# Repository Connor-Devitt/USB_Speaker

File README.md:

# USB_Speaker
Electro-mechanical design for a  USB spaker

## Electrical Design
* Designed for single cable operation
* USB powered with on-board USB to audio DAC and stereo audio amplifier
* 2 18650 batteries for high power amplifier
* USB charges batteries when speaker is idle

### The Schematic (v0.1)

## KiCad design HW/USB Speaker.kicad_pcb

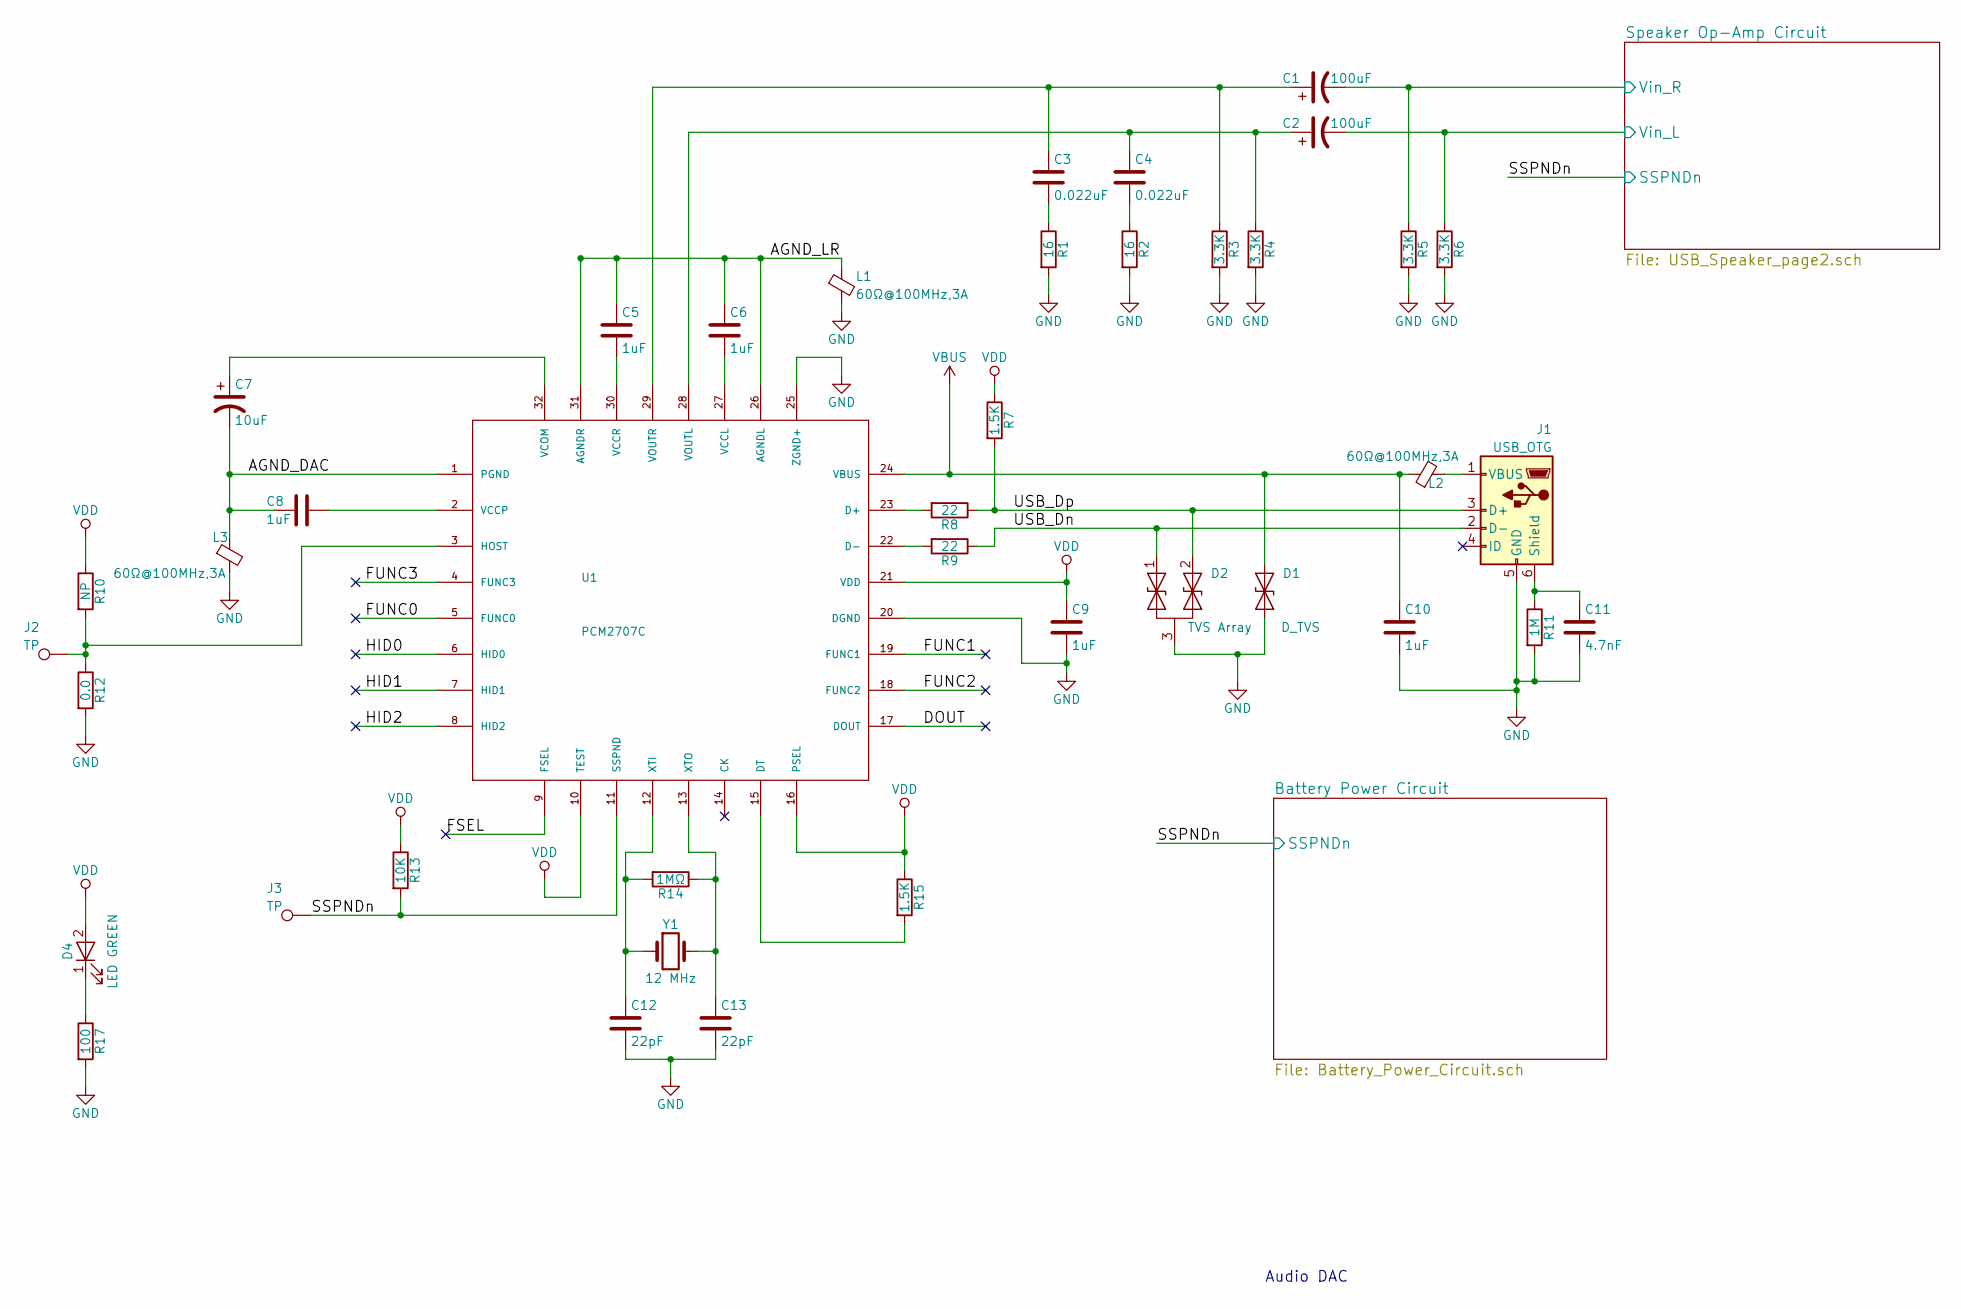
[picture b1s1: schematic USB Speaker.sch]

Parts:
C1, C2: 100uF; CP_Elec_6.3x5.7
C3, C4: 0.022uF; C_0805_HandSoldering
C5, C6, C8, C9, C10: 1uF; C_0805_HandSoldering
C7: 10uF; CP_Elec_6.3x5.7
C11: 4.7nF; C_0805_HandSoldering
C12, C13: 22pF; C_0805_HandSoldering
D1: D_TVS; D_SC79
D2: TVS Array; SOT-23
D4: LED GREEN; D_0805
J1: USB_OTG; USB_miniB_hirose_5S8
J2, J3: TP; Measurement_Point_Round-TH_Big
L1, L2, L3: 60Ω@100MHz,3A; L_0805_HandSoldering
R1, R2: 16; R_0805_HandSoldering
R3, R4, R5, R6: 3.3K; R_0805_HandSoldering
R7, R15: 1.5K; R_0805_HandSoldering
R8, R9: 22; R_0805_HandSoldering
R10: NP; R_0805_HandSoldering
R11: 1M; R_0805_HandSoldering
R12: 0.0; R_0805_HandSoldering
R13: 10K; R_0805_HandSoldering
R14: 1MΩ; R_0805_HandSoldering
R17: 100; R_0805_HandSoldering
U1: PCM2707C; TQFP-32_7x7mm_Pitch0.8mm
Y1: 12 MHz; Crystal_HC49-4H_Vertical

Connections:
/AGND_DAC: C7.2, C8.2, L3.1, U1.1 (PGND)
/AGND_LR: C5.1, C6.1, L1.1, U1.26 (AGNDL), U1.31 (AGNDR)
/DOUT: U1.17 (DOUT)
/FSEL: U1.9 (FSEL)
/FUNC0: U1.5 (FUNC0)
/FUNC1: U1.19 (FUNC1)
/FUNC2: U1.18 (FUNC2)
/FUNC3: U1.4 (FUNC3)
/HID0: U1.6 (HID0)
/HID1: U1.7 (HID1)
/HID2: U1.8 (HID2)
/SSPNDn: J3.1, R13.2, U1.11 (SSPND); also elsewhere on the board
/Speaker Op-Amp Circuit/Vin_L: C2.2, R6.1; also elsewhere on the board
/Speaker Op-Amp Circuit/Vin_R: C1.2, R5.1; also elsewhere on the board
/USB_Dn: D2.1 (A1), J1.2 (D-), R9.1
/USB_Dp: D2.2 (A2), J1.3 (D+), R7.2, R8.1
GND: C9.2, C10.2, C11.2, C12.2, C13.2, D1.1 (A1), D2.3 (common), J1.5 (GND), L1.2, L3.2, R1.2, R2.2, R3.2, R4.2, R5.2, R6.2, R11.2, R12.2, R17.2, U1.20 (DGND), U1.25 (ZGND+); also elsewhere on the board
unnamed: C1.1, C3.1, R3.1, U1.29 (VOUTR)
unnamed: C2.1, C4.1, R4.1, U1.28 (VOUTL)
unnamed: C3.2, R1.1
unnamed: C4.2, R2.1
unnamed: C5.2, U1.30 (VCCR)
unnamed: C6.2, U1.27 (VCCL)
unnamed: C7.1, U1.32 (VCOM)
unnamed: C8.1, U1.2 (VCCP)
unnamed: C11.1, J1.6 (Shield), R11.1
unnamed: C12.1, R14.2, U1.12 (XTI), Y1.1
unnamed: C13.1, R14.1, U1.13 (XTO), Y1.2
unnamed: D4.1 (K), R17.1
unnamed: J1.1 (VBUS), L2.2
unnamed: J2.1, R10.2, R12.1, U1.3 (HOST)
unnamed: R8.2, U1.23 (D+)
unnamed: R9.2, U1.22 (D-)
unnamed: R15.2, U1.15 (DT)
VBUS: C10.1, D1.2 (A2), L2.1, U1.24 (VBUS); also elsewhere on the board
VDD: C9.1, D4.2 (A), R7.1, R10.1, R13.1, R15.1, U1.10 (TEST), U1.16 (PSEL), U1.21 (VDD)

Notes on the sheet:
Audio DAC

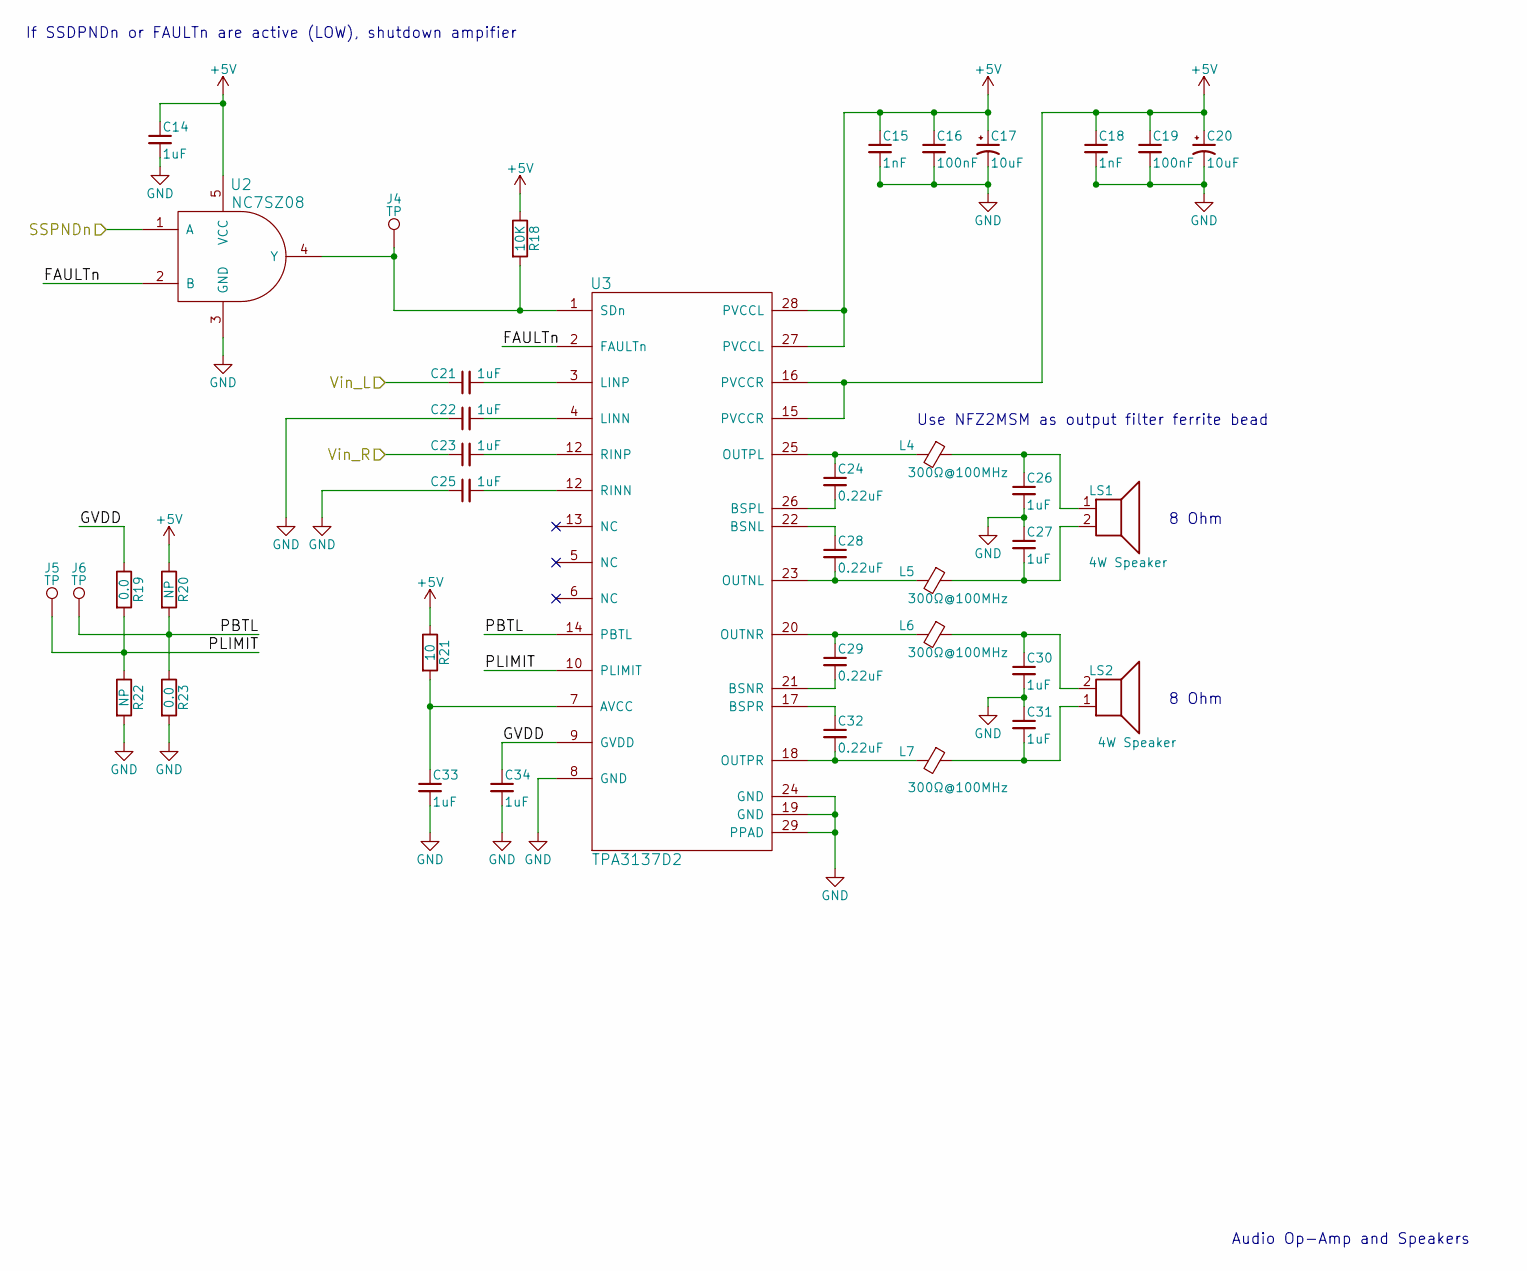
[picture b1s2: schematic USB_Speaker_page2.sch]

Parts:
C14, C21, C22, C23, C25, C26, C27, C30, C31, C33, C34: 1uF; C_0805_HandSoldering
C15, C18: 1nF; C_0805_HandSoldering
C16, C19: 100nF; C_0805_HandSoldering
C17, C20: 10uF; CP_Elec_6.3x5.7
C24, C28, C29, C32: 0.22uF; C_0805_HandSoldering
J4, J5, J6: TP; Measurement_Point_Round-TH_Big
L4, L5, L6, L7: 300Ω@100MHz; L_0805_HandSoldering
LS1, LS2: 4W Speaker; TerminalBlock_bornier-2_P5.08mm
R18: 10K; R_0805_HandSoldering
R19, R23: 0.0; R_0805_HandSoldering
R20, R22: NP; R_0805_HandSoldering
R21: 10; R_0805_HandSoldering
U2: NC7SZ08; SOT-23-5_HandSoldering
U3: TPA3137D2; TSSOP-28_4.4x9.7mm_Pitch0.65mm

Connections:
+5V: C14.1, C15.1, C16.1, C17.1, C18.1, C19.1, C20.1, R18.1, R20.1, R21.1, U2.5 (VCC), U3.15 (PVCCR), U3.16 (PVCCR), U3.27 (PVCCL), U3.28 (PVCCL); also elsewhere on the board
/SSPNDn: U2.1 (A); also elsewhere on the board
/Speaker Op-Amp Circuit/FAULTn: U2.2 (B), U3.2 (FAULTn)
/Speaker Op-Amp Circuit/GVDD: C34.1, R19.1, U3.9 (GVDD)
/Speaker Op-Amp Circuit/PBTL: J6.1, R20.2, R23.1, U3.14 (PBTL)
/Speaker Op-Amp Circuit/PLIMIT: J5.1, R19.2, R22.1, U3.10 (PLIMIT)
/Speaker Op-Amp Circuit/Vin_L: C21.1; also elsewhere on the board
/Speaker Op-Amp Circuit/Vin_R: C23.1; also elsewhere on the board
GND: C14.2, C15.2, C16.2, C17.2, C18.2, C19.2, C20.2, C22.1, C25.1, C26.2, C27.1, C30.2, C31.1, C33.2, C34.2, R22.2, R23.2, U2.3 (GND), U3.8 (GND), U3.19 (GND), U3.24 (GND), U3.29 (PPAD); also elsewhere on the board
unnamed: C21.2, U3.3 (LINP)
unnamed: C22.2, U3.4 (LINN)
unnamed: C24.1, L4.2, U3.25 (OUTPL)
unnamed: C24.2, U3.26 (BSPL)
unnamed: C26.1, L4.1, LS1.1
unnamed: C27.2, L5.1, LS1.2
unnamed: C28.1, U3.22 (BSNL)
unnamed: C28.2, L5.2, U3.23 (OUTNL)
unnamed: C29.1, L6.2, U3.20 (OUTNR)
unnamed: C29.2, U3.21 (BSNR)
unnamed: C30.1, L6.1, LS2.2
unnamed: C31.2, L7.1, LS2.1
unnamed: C32.1, U3.17 (BSPR)
unnamed: C32.2, L7.2, U3.18 (OUTPR)
unnamed: C33.1, R21.2, U3.7 (AVCC)
unnamed: J4.1, R18.2, U2.4 (Y), U3.1 (SDn)

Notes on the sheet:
Audio Op-Amp and Speakers
Use NFZ2MSM as output filter ferrite bead
If SSDPNDn or FAULTn are active (LOW), shutdown ampifier
8 Ohm

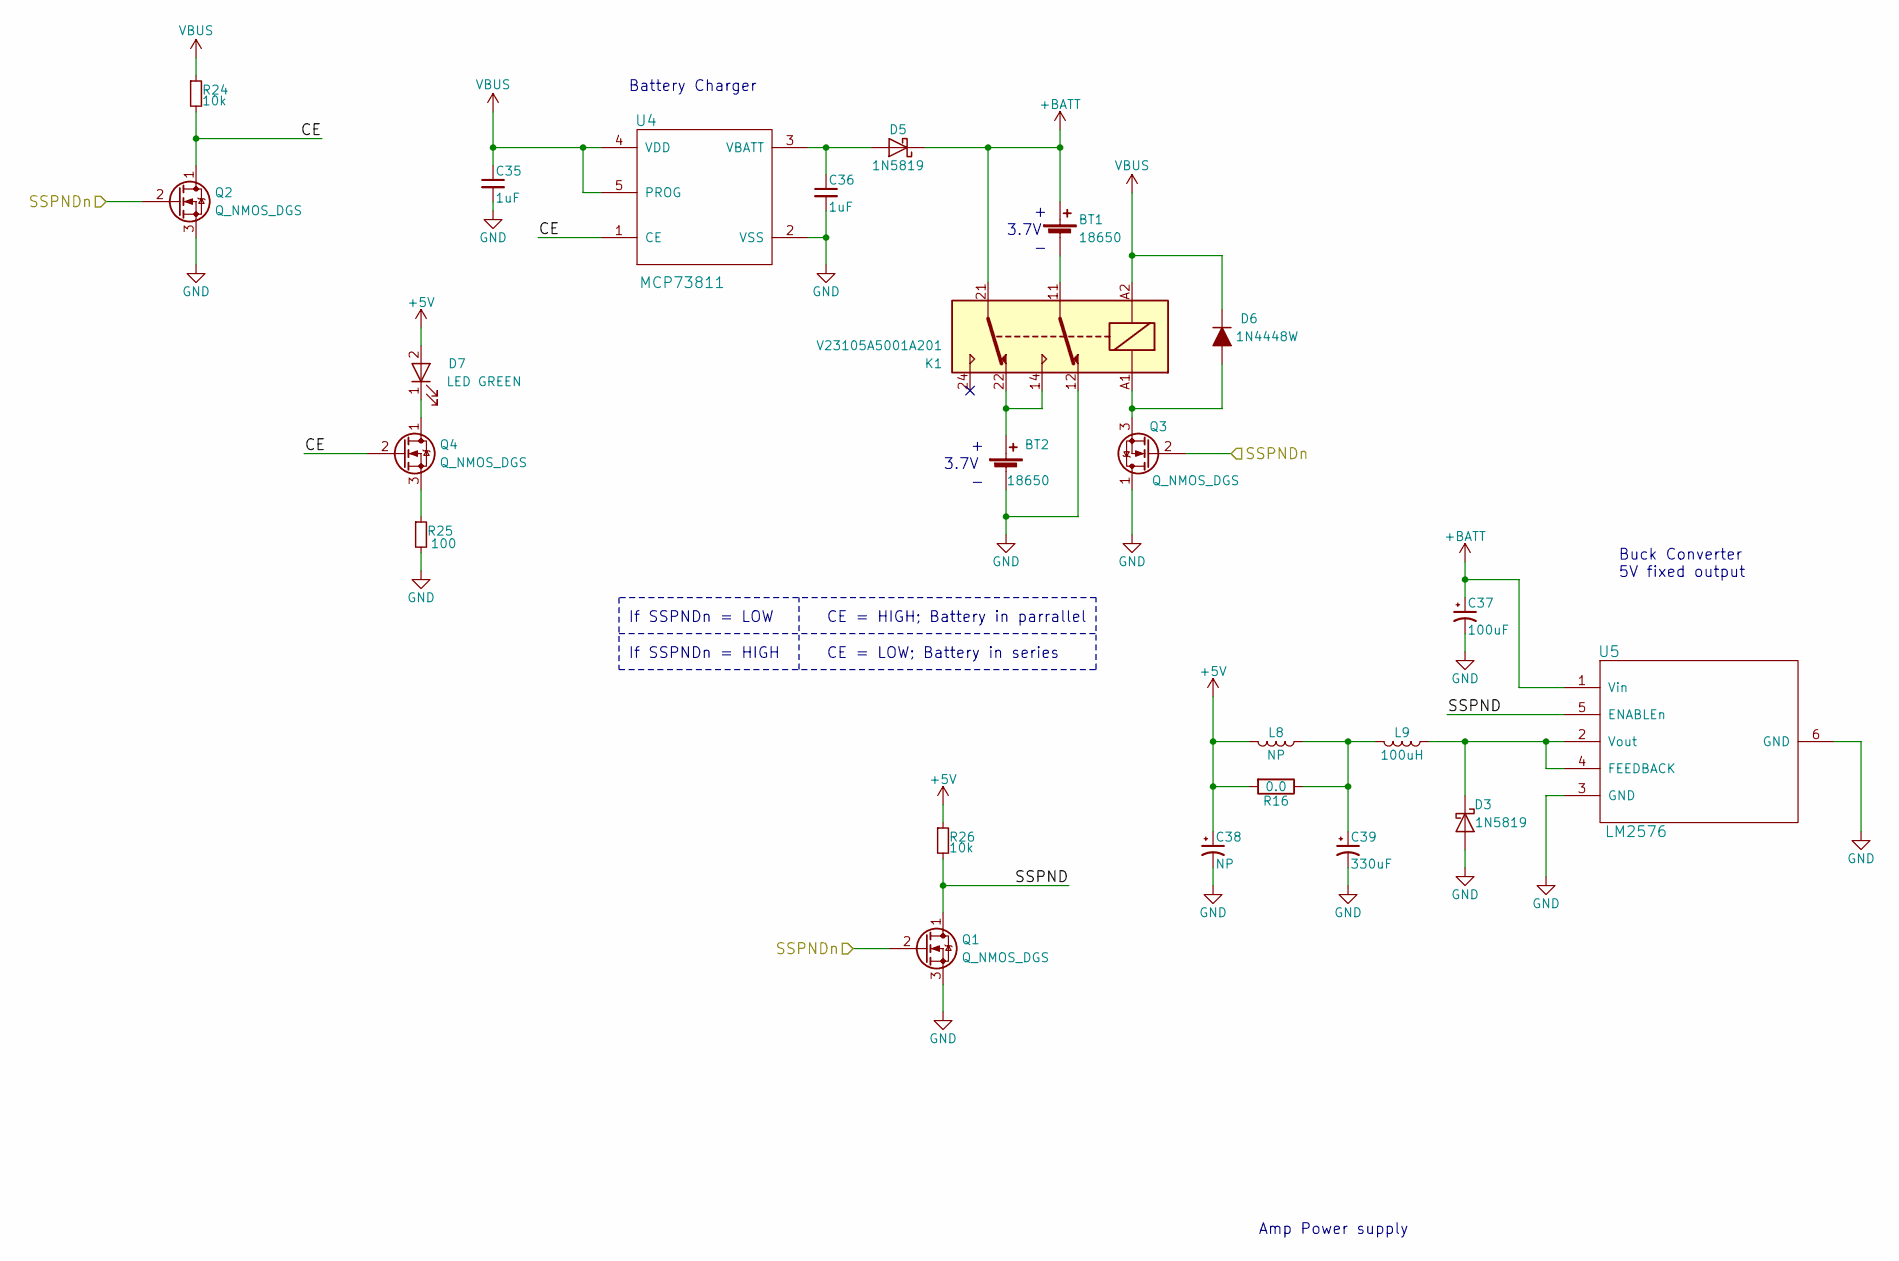
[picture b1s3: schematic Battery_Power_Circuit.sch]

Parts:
BT1, BT2: 18650; TerminalBlock_bornier-2_P5.08mm
C35, C36: 1uF; C_0805_HandSoldering
C37: 100uF; CP_Elec_6.3x5.7
C38: NP; CP_Elec_6.3x5.7
C39: 330uF; CP_Elec_6.3x7.7
D3, D5: 1N5819; D_SOD-123
D6: 1N4448W; D_SOD-123
D7: LED GREEN; D_0805
K1: V23105A5001A201; Relay_DPDT_Finder_40.52
L8: NP; L_12x12mm_h4.5mm
L9: 100uH; L_12x12mm_h8mm
Q1, Q2, Q3, Q4: Q_NMOS_DGS; SOT-23_Handsoldering
R16: 0.0; R_0805_HandSoldering
R24, R26: 10k; R_0805_HandSoldering
R25: 100; R_0805_HandSoldering
U4: MCP73811; SOT-23-5_HandSoldering
U5: LM2576; TO-263-5_TabPin6

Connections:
+5V: C38.1, D7.2 (A), L8.2, R16.2, R26.1; also elsewhere on the board
+BATT: BT1.1 (+), C37.1, D5.1 (K), K1.21, U5.1 (Vin)
/Battery Power Circuit/CE: Q2.1 (D), Q4.2 (G), R24.2, U4.1 (CE)
/Battery Power Circuit/SSPND: Q1.1 (D), R26.2, U5.5 (ENABLEn)
/SSPNDn: Q1.2 (G), Q2.2 (G), Q3.2 (G); also elsewhere on the board
GND: BT2.2 (-), C35.2, C36.2, C37.2, C38.2, C39.2, D3.2 (A), K1.12, Q1.3 (S), Q2.3 (S), Q3.1 (D), R25.2, U4.2 (VSS), U5.3 (GND), U5.6 (GND); also elsewhere on the board
unnamed: BT1.2 (-), K1.11
unnamed: BT2.1 (+), K1.14, K1.22
unnamed: C36.1, D5.2 (A), U4.3 (VBATT)
unnamed: C39.1, L8.1, L9.2, R16.1
unnamed: D3.1 (K), L9.1, U5.2 (Vout), U5.4 (FEEDBACK)
unnamed: D6.2 (A), K1.A1, Q3.3 (S)
unnamed: D7.1 (K), Q4.1 (D)
unnamed: Q4.3 (S), R25.1
VBUS: C35.1, D6.1 (K), K1.A2, R24.1, U4.4 (VDD), U4.5 (PROG); also elsewhere on the board

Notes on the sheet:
Amp Power supply
If SSPNDn = LOW
If SSPNDn = HIGH
CE = HIGH; Battery in parrallel
CE = LOW; Battery in series
3.7V
Battery Charger
Buck Converter 5V fixed output

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
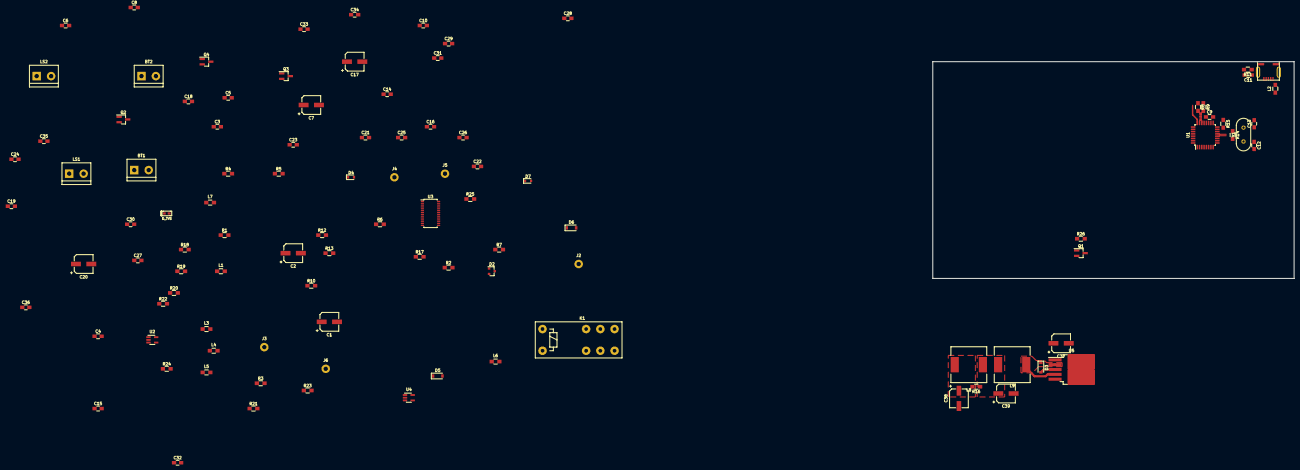
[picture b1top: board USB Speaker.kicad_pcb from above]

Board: 2 copper layers, 127.0 x 76.2 mm, 102 parts (0 on the bottom side), 60 nets.

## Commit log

2018-06-06 Added PCM2707 to sch
2018-06-07 Clock and USB circuits
2018-06-09 DAC circuit
2018-06-14 DAC circuit edits and op-amp symbol creation
2018-06-19 Amplifier circuit using TPA6211A1-Q1
2018-06-20 Switching out 2x TPA6211A1 for 1x TPA3137D2
2018-06-21 Finsihed drawing amp circuit. Adding options and values later
2018-06-24 ferrite chosen
2018-06-27 Basic battery power supply topology
2018-06-28 What did I do?
2018-07-04 Added LEDs, Test points, and ESD protection on USB
2018-07-08 First draft done :100:
2018-07-08 Added detail to readme
2018-07-08 Added schematic in png form
2018-07-08 Changes pdf to png
2018-07-08 First :b:raft 4realz :100:
2018-07-08 Files not updating
2018-07-08 Deleted an empty page
2018-07-08 :b:low my brains out
2018-07-10 7V Regulator now a 5V buck converter
2018-07-10 updated image
2018-07-10 Buck and fp
    Changed buck to one with 3A output. Started fp association
2018-07-17 parts association and some selection
2018-07-17 initial layout
